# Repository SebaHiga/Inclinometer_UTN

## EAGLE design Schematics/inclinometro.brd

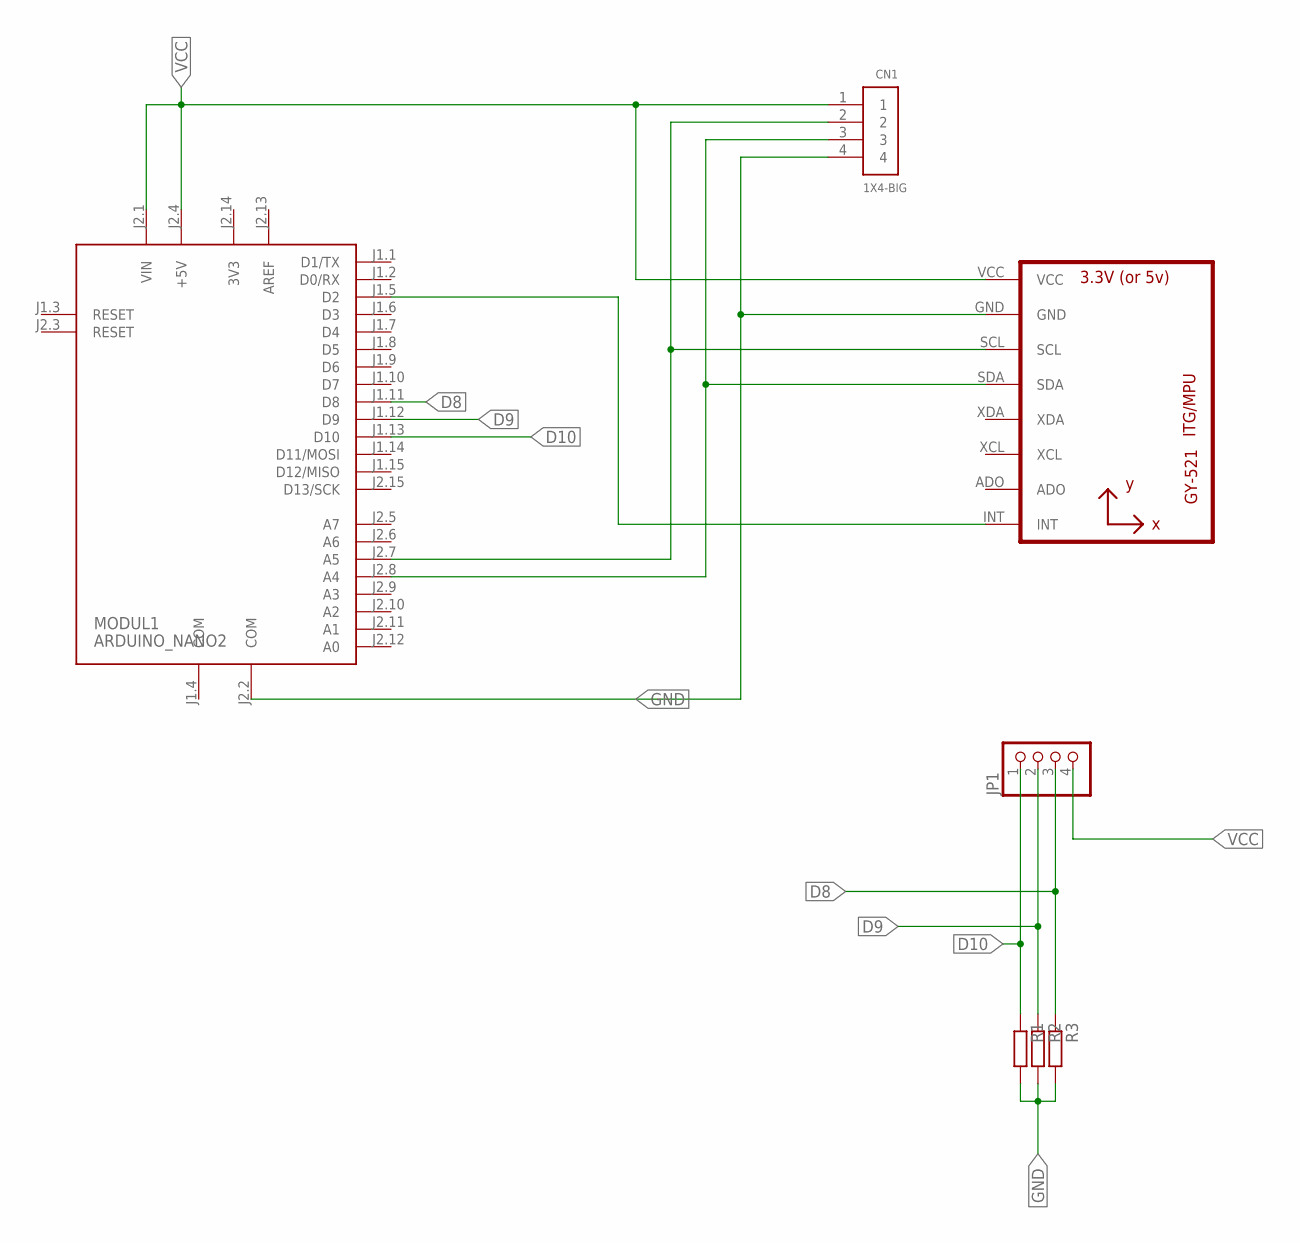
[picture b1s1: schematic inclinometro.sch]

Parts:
CN1: 1X4-BIG; 1X04-BIG
JP1: PINHD-1X4; 1X04
MODUL1: ARDUINO_NANO2
R1, R2, R3: R-EU_0207/10; 0207/10
U1: GY-521MPU6050; GY-521

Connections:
3V3: MODUL1.J2.14 (3V3)
AREF: MODUL1.J2.13 (AREF)
COM: MODUL1.J1.4 (COM)
D8: JP1.3, MODUL1.J1.11 (D8), R3.1
D9: JP1.2, MODUL1.J1.12 (D9), R2.1
D10: JP1.1, MODUL1.J1.13 (D10), R1.1
GND: CN1.4, MODUL1.J2.2 (COM), R1.2, R2.2, R3.2, U1.GND
unnamed: CN1.3, MODUL1.J2.8 (A4), U1.SDA
unnamed: CN1.2, MODUL1.J2.7 (A5), U1.SCL
unnamed: MODUL1.J1.5 (D2), U1.INT
VCC: CN1.1, JP1.4, MODUL1.J2.1 (VIN), MODUL1.J2.4 (+5V), U1.VCC

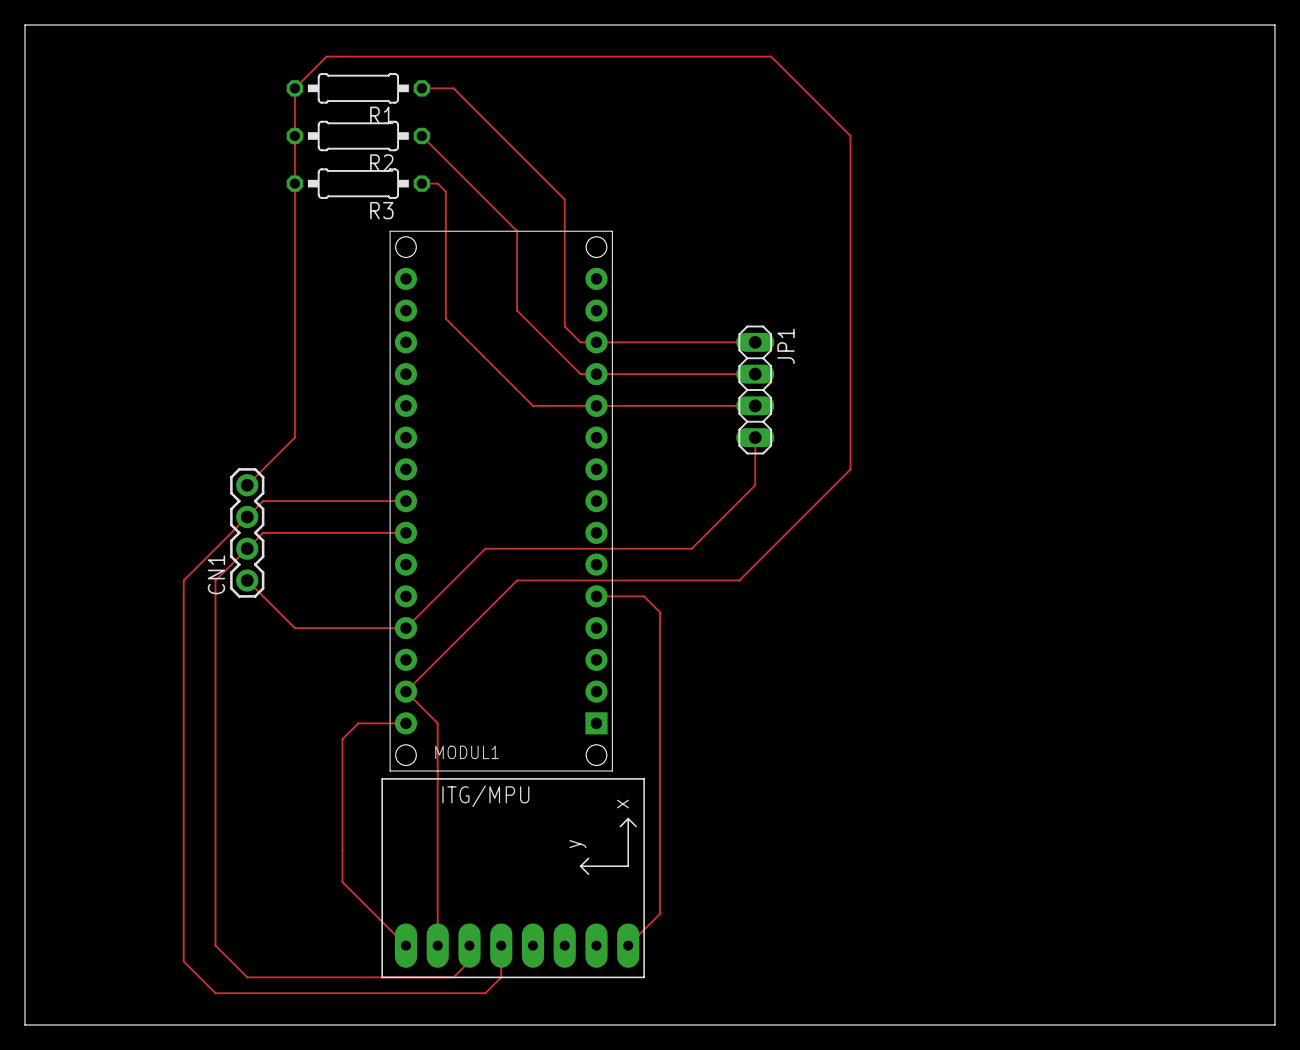
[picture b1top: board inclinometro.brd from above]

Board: 2 copper layers, 100.0 x 80.0 mm, 7 parts (0 on the bottom side), 8 nets.

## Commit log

2020-07-27 Changed uC to Arduino nano
2020-07-27 changed for loop to for each based with no initializer
2020-07-28 Added schematics to repository
2020-08-12 Included FreeRTOS to project
2020-08-12 moved mpu6050 pragma once to tp
2020-08-12 Creation of task for acceleration measure
2020-08-12 Stack debug: debug flag on build_flags
2020-08-12 Comment build flags to reduce verbosity
2020-08-12 Feature/free rtos (#1)
    * Included FreeRTOS to project
    * moved mpu6050 pragma once to tp
    * Creation of task for acceleration measure
    * Stack debug: debug flag on build_flags
    * Comment build flags to reduce verbosity
2020-08-12 Templated rawvector, using int16_t
2020-08-12 Print formatted mode to console
2020-08-12 Change on rawvect now it's properly templated
2020-08-12 Add LSB constant from manual
2020-08-12 Print formatted function
2020-08-12 Moved geometry as library
2020-08-13 Added buttons
2020-08-14 Created MPU6050.cpp
2020-08-14 Adding semaphore interaction demo between button and mpu display
2020-08-14 Feature/mpu6050 (#2)
    * Templated rawvector, using int16_t
    * Print formatted mode to console
    * Change on rawvect now it's properly templated
    * Add LSB constant from manual
    * Print formatted function
    * Moved geometry as library
2020-08-14 fixing buttons header file name
2020-08-14 lcd hello world
2020-08-14 size of main tasks reduced
2020-08-14 Increased wait time for button and lcd
2020-08-14 Now read MPU is not dependant of Accel task
2020-08-15 Feature/lcd (#3)
    * fixing buttons header file name
    * lcd hello world
    * size of main tasks reduced
    * Increased wait time for button and lcd
    * Now read MPU is not dependant of Accel task
2020-08-16 Print accel output at 100hz
2020-08-16 Noise analysis with jupyter notebooks
2020-08-16 add notebooks ignore
2020-08-16 Feature/noise analysis (#4)
    * Print accel output at 100hz
    * Noise analysis with jupyter notebooks
    * add notebooks ignore
2020-08-17 Filter template with templated array
2020-08-17 Fixed oorder initalization error with array lengths Added array´s default constructor
2020-08-17 Setting up for filter order 3
2020-08-17 Bugfix on overwritting coefficients array
2020-08-17 Print filter output
2020-08-17 Feature/lowpass filter (#5)
    * Filter template with templated array
    * Fixed oorder initalization error with array lengths
    Added array´s default constructor
    * Setting up for filter order 3
    * Bugfix on overwritting coefficients array
    * Print filter output
2020-08-17 Create LICENSE
2020-08-17 Create LICENSE (#6)
2020-08-18 abstract array logic to mpu
2020-08-18 change order of filter to 2
2020-08-18 change display mode to y axis
2020-08-18 change analysis to y axis and print b and a coefficients
2020-08-18 Quick redo/filter (#7)
    * abstract array logic to mpu
    * change order of filter to 2
    * change display mode to y axis
    * change analysis to y axis and print b and a coefficients
2020-08-18 Print 3 axis vector
2020-08-18 add filter per axis
2020-08-18 Feature/multi filter (#8)
    * Print 3 axis vector
    * add filter per axis
2020-08-18 Accel filtered is now global variable
2020-08-18 Print filtered x axis on screen
2020-08-29 Modified to filter acceleration with floating point
2020-08-29 Feature/show display (#9)
    * Accel filtered is now global variable
    * Print filtered x axis on screen
    * Modified to filter acceleration with floating point
2020-08-29 std range class
2020-08-29 Implementing resersing option on std::range
2020-08-29 Added negative ranging
2020-08-29 Redo/arrays (#10)
    * std range class
    * Implementing resersing option on std::range
    * Added negative ranging
2020-10-15 First schematics
2020-10-19 Changes on screw diameter
2020-10-20 Curve fit analysis
2020-10-27 Static analysis for resulting angle
2020-10-27 Update on case
2020-10-27 Print angle with linear regression
2020-11-13 zero offset with very weird changes
2020-11-14 showing bubble and ceil implementation
2020-11-14 two axis implementation
2020-11-15 ceil and regression analysis plot complete
2020-11-15 lcd details
2020-11-15 reduced to 2 hz
2020-11-15 bubble sensitivity
2020-12-19 last commit from 2020 i guess
